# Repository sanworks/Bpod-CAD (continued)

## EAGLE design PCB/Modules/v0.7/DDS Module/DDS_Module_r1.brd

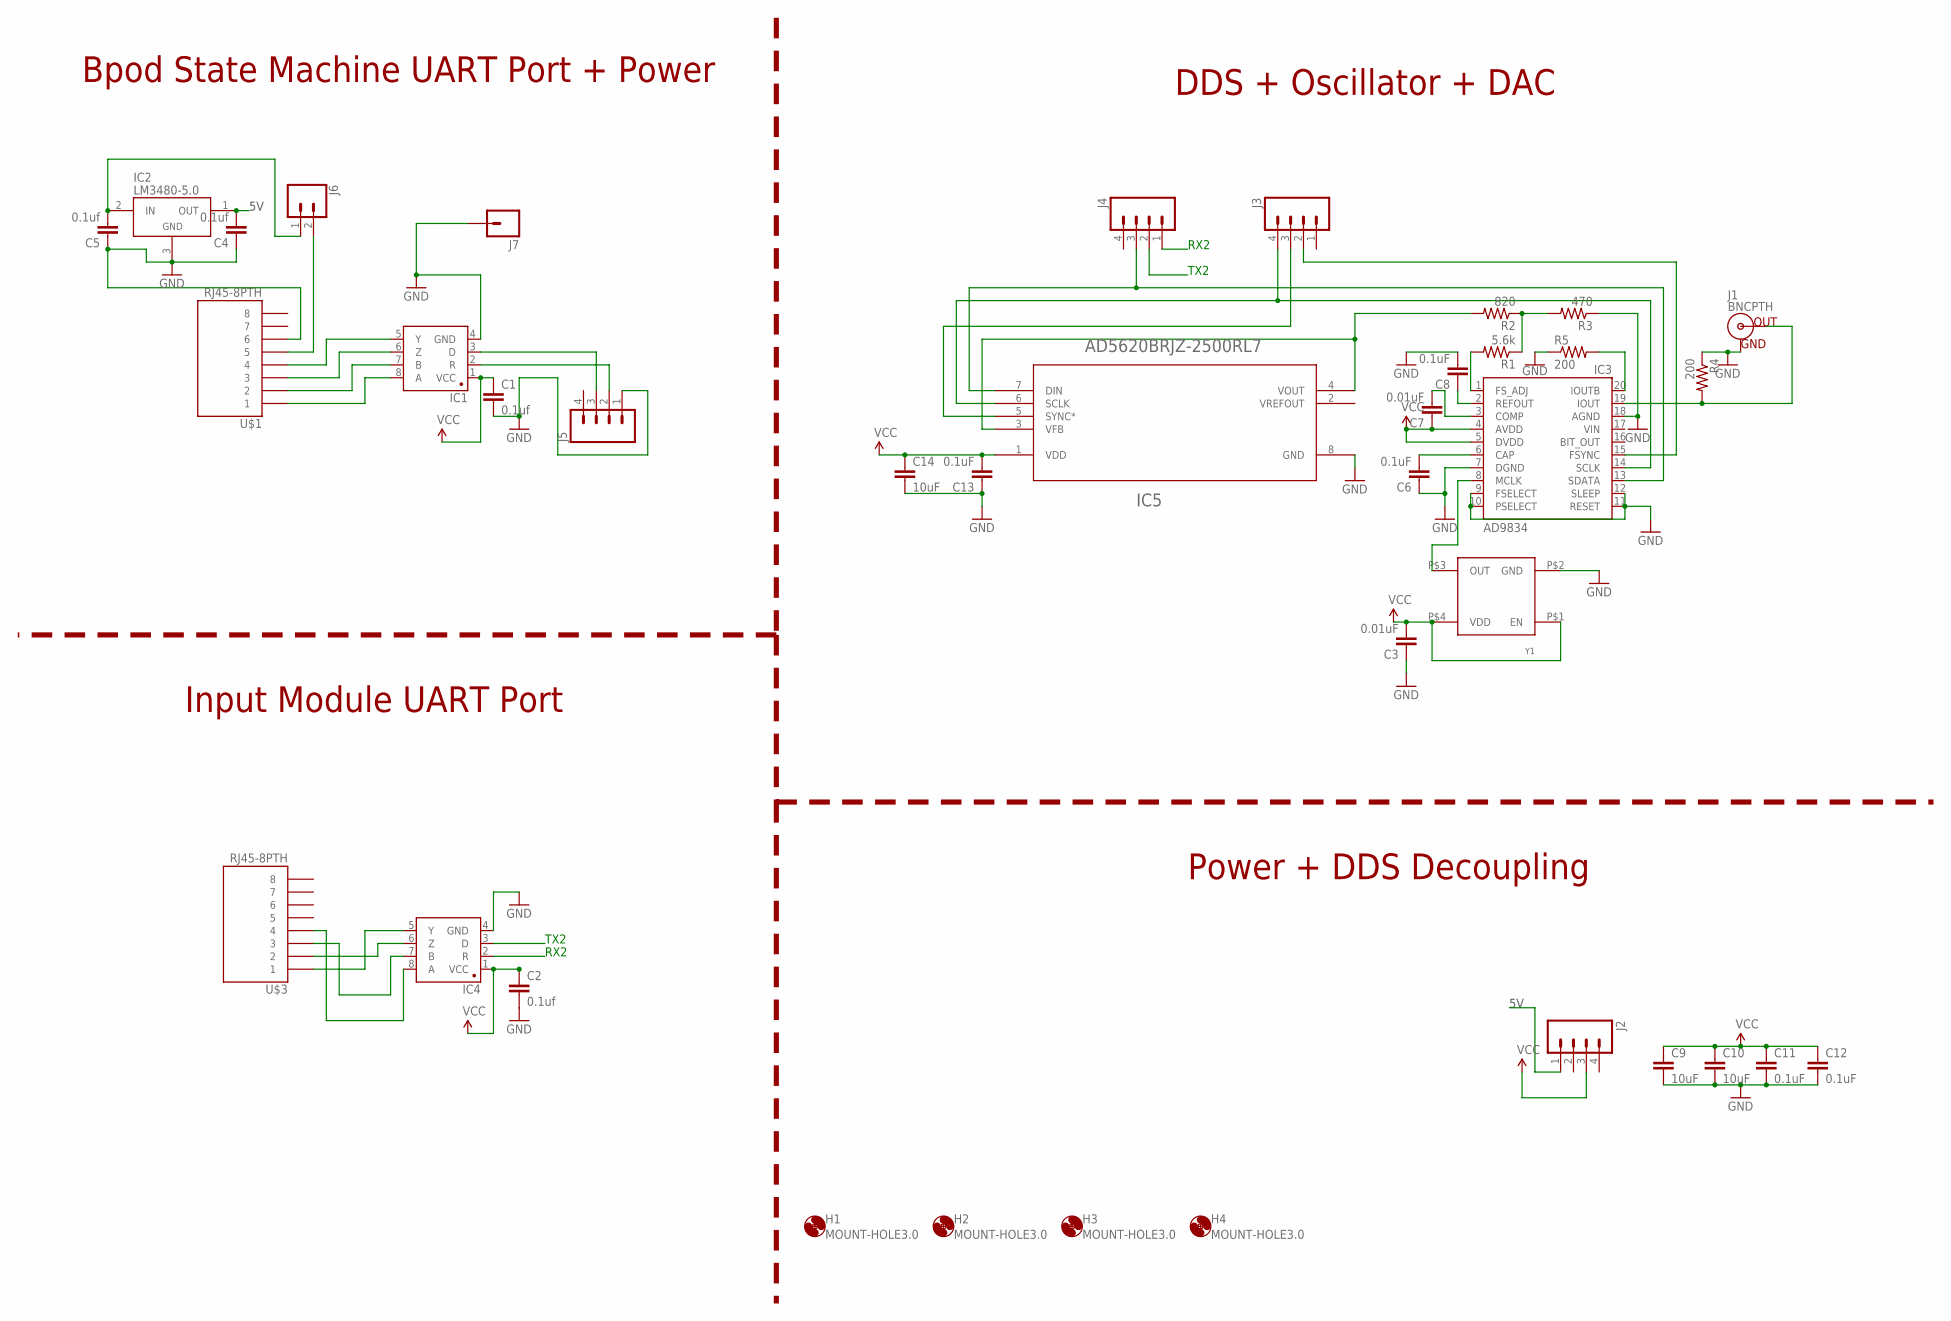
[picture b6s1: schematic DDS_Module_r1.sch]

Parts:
C1, C2, C4, C5: 0.1uf; 1206@1
C3, C7: 0.01uF; 0805
C6, C8, C11, C12, C13: 0.1uF; 0805
C9, C10, C14: 10uF; 0805
H1, H2, H3, H4: MOUNT-HOLE3.0; 3,0
IC1, IC4: SN65HVD31DR; SO08
IC2: LM3480-5.0; SOT-23-3
IC3: AD9834; TSSOP20
IC5: AD5620BRJZ-2500RL7; RJ_8
J1: BNCPTH; BNC
J2, J3, J4, J5: M04PTH; 1X04
J6: CONN_02; 1X02
J7: M01PTH; 1X01
R1: 5.6k; R0805
R2: 820; R0805
R3: 470; R0805
R4, R5: 200; R0805
U$1, U$3: RJ45-8PTH; RJ45-8
Y1: ASE10MHZ

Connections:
5V: C4.2, IC2.1 (OUT), J2.1
GND: C1.2, C2.2, C3.1, C4.1, C5.1, C6.1, C8.2, C9.2, C10.2, C11.2, C12.2, C13.1, C14.2, IC1.4 (GND), IC2.3 (GND), IC3.7 (DGND), IC3.9 (FSELECT), IC3.10 (PSELECT), IC3.11 (RESET), IC3.12 (SLEEP), IC3.18 (AGND), IC4.4 (GND), IC5.8 (GND), J1.GND, J5.1, J7.1, R3.1, R4.1, R5.1, U$1.6, Y1.P$2 (GND)
unnamed: IC3.13 (SDATA), IC5.7 (DIN), J4.3
unnamed: IC3.14 (SCLK), IC5.6 (SCLK), J3.4
unnamed: IC5.5 (SYNC*), J3.3
unnamed: IC3.20 (IOUTB), R5.2
unnamed: IC3.15 (FSYNC), J3.2
unnamed: IC1.8 (A), U$1.1
unnamed: IC1.7 (B), U$1.2
unnamed: IC1.6 (Z), U$1.3
unnamed: IC1.5 (Y), U$1.4
unnamed: IC5.3 (VFB), IC5.4 (VOUT), R2.2
unnamed: IC3.8 (MCLK), Y1.P$3 (OUT)
unnamed: IC3.19 (IOUT), J1.S (OUT), R4.2
unnamed: C6.2, IC3.6 (CAP)
unnamed: C7.2, IC3.3 (COMP)
unnamed: C8.1, IC3.2 (REFOUT)
unnamed: IC3.1 (FS_ADJ), R1.2
unnamed: R1.1, R2.1, R3.2
unnamed: IC4.5 (Y), U$3.1
unnamed: IC4.6 (Z), U$3.2
unnamed: IC4.7 (B), U$3.3
unnamed: J6.2, U$1.5
unnamed: IC4.8 (A), U$3.4
unnamed: C5.2, IC2.2 (IN), J6.1
RX1: IC1.2 (R), J5.2
RX2: IC4.2 (R), J4.1
TX1: IC1.3 (D), J5.3
TX2: IC4.3 (D), J4.2
VCC: C1.1, C2.1, C3.2, C7.1, C9.1, C10.1, C11.1, C12.1, C13.2, C14.1, IC1.1 (VCC), IC3.4 (AVDD), IC3.5 (DVDD), IC4.1 (VCC), IC5.1 (VDD), J2.3, Y1.P$1 (EN), Y1.P$4 (VDD)

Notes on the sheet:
RX2
TX2
Bpod State Machine UART Port + Power
Input Module UART Port
DDS + Oscillator + DAC
Power + DDS Decoupling

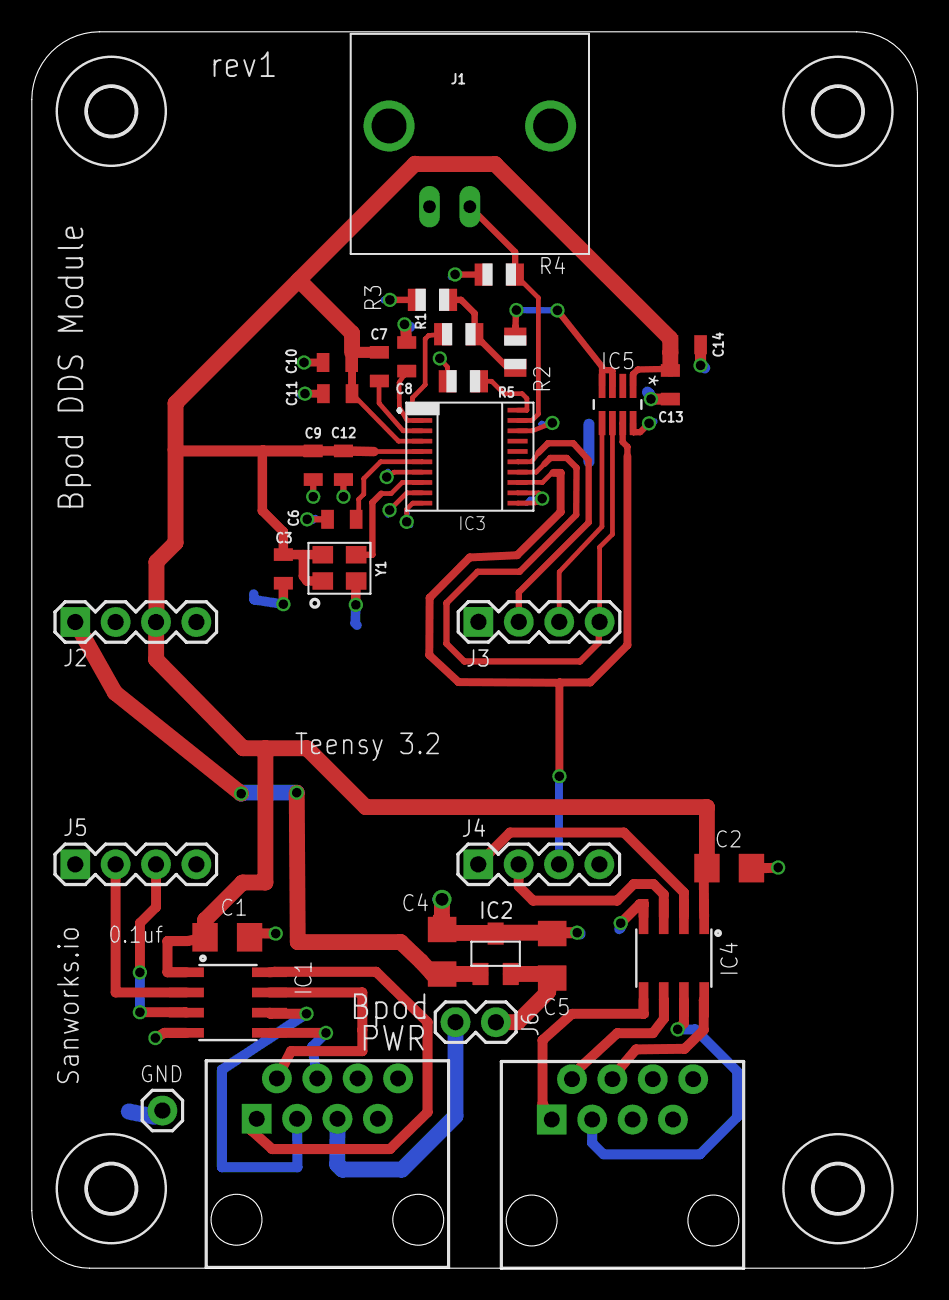
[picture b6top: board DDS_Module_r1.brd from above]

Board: 2 copper layers, 55.7 x 77.8 mm, 38 parts (0 on the bottom side), 30 nets.

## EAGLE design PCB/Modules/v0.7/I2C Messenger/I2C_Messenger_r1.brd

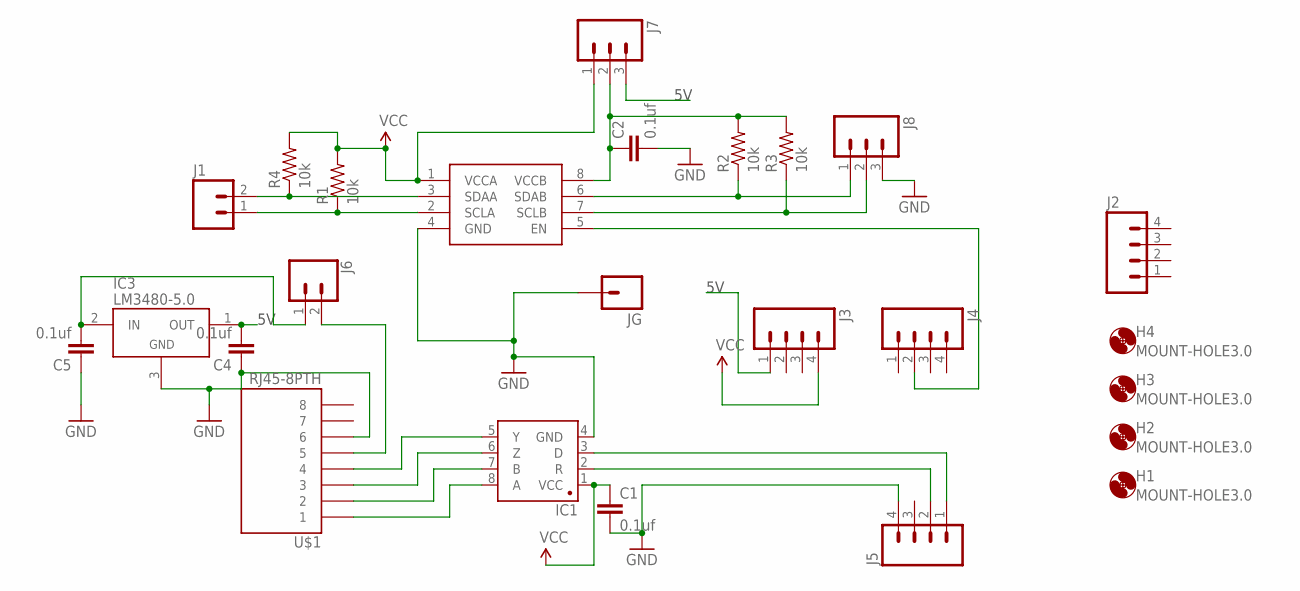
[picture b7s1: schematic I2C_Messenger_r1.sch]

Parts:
C1, C2, C4, C5: 0.1uf; 1206
H1, H2, H3, H4: MOUNT-HOLE3.0; 3,0
IC1: SN65HVD31DR; SO08
IC2: PCA9517; SO-08
IC3: LM3480-5.0; SOT-23-3
J1: M02PTH; 1X02@1
J2, J3, J4, J5: M04PTH; 1X04
J6: CONN_02; 1X02
J7: M03PTH; 1X03
J8: M03SCREW_LOCK; SCREWTERMINAL-3.5MM-3_LOCK.007S
JG: M01PTH; 1X01
R1, R2, R3, R4: 10k; 1206
U$1: RJ45-8PTH; RJ45-8

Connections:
5V: C4.2, IC3.1 (OUT), J3.1, J7.3
GND: C1.2, C2.2, C4.1, C5.1, IC1.4 (GND), IC2.4 (GND), IC3.3 (GND), J5.4, J8.3, JG.1, U$1.6
unnamed: J6.2, U$1.5
unnamed: IC1.3 (D), J5.1
unnamed: IC2.2 (SCLA), J1.1, R1.1
unnamed: IC1.2 (R), J5.2
unnamed: IC1.8 (A), U$1.1
unnamed: IC1.7 (B), U$1.2
unnamed: IC1.6 (Z), U$1.3
unnamed: IC1.5 (Y), U$1.4
unnamed: IC2.3 (SDAA), J1.2, R4.1
unnamed: C2.1, IC2.8 (VCCB), J7.2, R2.2, R3.2
unnamed: IC2.5 (EN), J4.2
unnamed: IC2.6 (SDAB), J8.1, R2.1
unnamed: IC2.7 (SCLB), J8.2, R3.1
unnamed: C5.2, IC3.2 (IN), J6.1
VCC: C1.1, IC1.1 (VCC), IC2.1 (VCCA), J3.4, J7.1, R1.2, R4.2

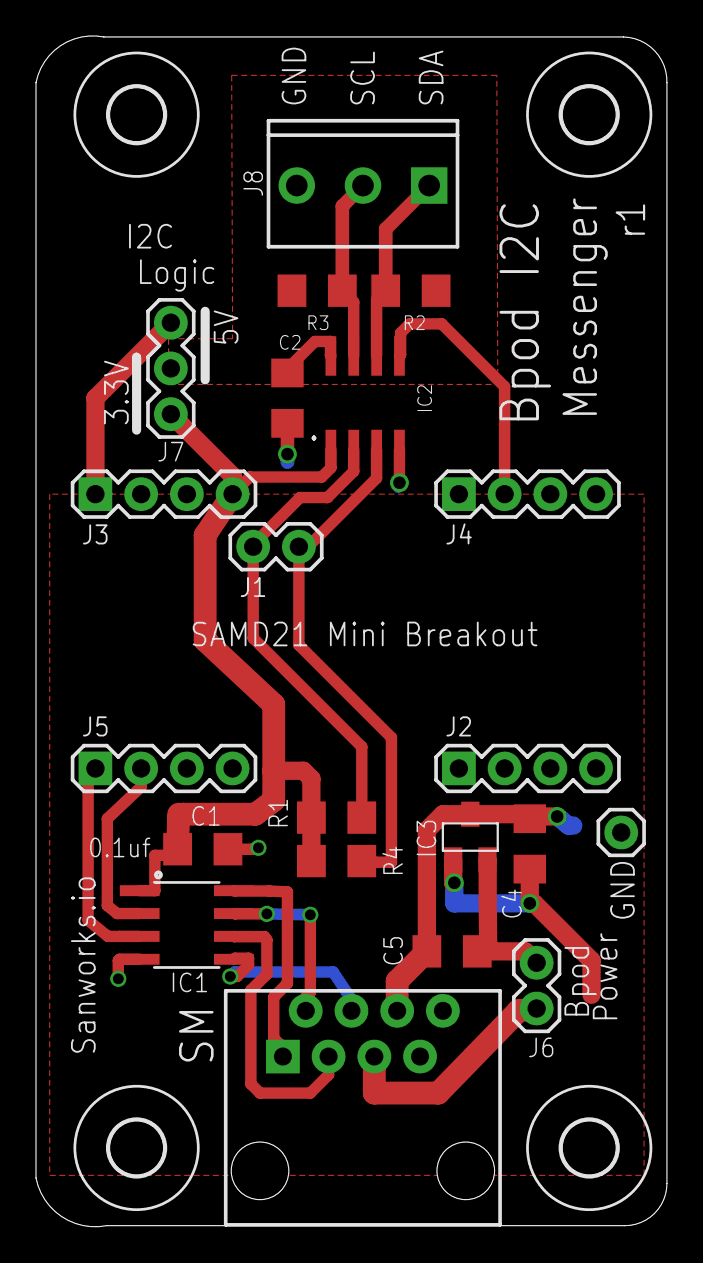
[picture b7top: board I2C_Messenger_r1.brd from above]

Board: 2 copper layers, 35.1 x 66.1 mm, 25 parts (0 on the bottom side), 17 nets.
